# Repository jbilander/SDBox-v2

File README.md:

# SDBox v2
***
SDBox v2 for Amiga, hardware compatible with the new updated card-detect (insert/eject interrupt) firmware written by N.Ekström available here: https://github.com/niklasekstrom/amiga-par-to-spi-adapter

This version is superseded by the new SDBox-v3 here: https://github.com/jbilander/SDBox-v3
***

<br />

<br />

***

Here is a short video clip showing the new card detect feature: <br />
https://drive.google.com/file/d/11R0idJcfvWwsGSfzbPFG1xpoupvCA6SC/view?usp=sharing

***

### Howto build the SDBox Rev2...

***

Start by soldering the `U2` and `U3` ICs, then the passives, the card holder, micro-usb jack, DB25M and so on, nothing complicated, but do skip the 6-pin ICSP-header on the Nano if you're going to put this in a 3D-printed case...

***

***

At this stage, before you solder the Nano down to the board, you should verify that `+5V` via the Micro-USB jack is ok...

***

***

Now the Nano, validate `+5V` and `+3.3V` is ok on the Nano:

Powering the MicroSD card directly from the 3.3V-pin of the Arduino, are you nuts?

Well, maybe, but typical SD card current consumption is `~30mA` in SPI mode.
The Arduino Nano taps `3.3V` from the internal LDO `3V3OUT` supply of the `FT232RL` USB-chip, or in case of the clones the `CH340` USB-chip. 

    FT232RL: Up to 50mA can be drawn from this pin to power external logic if required.
    CH340G: Maximum output current is 30mA, and that voltage stays rather stable up to about 30mA.
***

***

Time to build and flash the firmware:

***

<br />

***

And we need to 3D-print a case for it before we put the LEDs in, don't we?...

(STL-files available in the DSM folder)

***

***

Final result:
<br />

***

Comparison with `v1`, look at the difference in size:
<br />

***

Now time to build the new `spisd.device` driver, add `+kick13` to the `build.bat` if default is set to build for AmigaOS 2.0...

(`VBCC` for Windows I downloaded from here (Thanks: Leffmann for the installer), https://eab.abime.net/showthread.php?t=83113 )

***

***

BOM Rev. 2A
---------
Position  | Name/Value   | Package | Notes
-|-|-|-|
U1 | Arduino Nano V3 | |
U2 | 74LVC3G17 | TSSOP-8_3x3mm_P0.65mm | Triple non-inverting Schmitt trigger with 5V tolerant input [74LVC3G17](https://www.mouser.com/ProductDetail/771-LVC3G17DP125)
U3 | 74AHCT1G17 | 5-TSSOP, SC-70-5, SOT-353  (2.0 mm × 1.25mm) | Single non-inverting Schmitt trigger [74AHCT1G17GWH](https://www.mouser.com/ProductDetail/771-74AHCT1G17GWH)
J1 | D-Sub DB25M | DB25 Male connector with solder lugs | DB25 for Amiga parallel port
J2 | Micro USB connector | USB Micro B SMT | For +5V Power, (style 1) <br />https://www.aliexpress.com/item/32991869539.html
J3 | Micro SD Card Holder | 9-pin Micro SD card slot connector | https://www.aliexpress.com/item/32802051702.html
D1 (Optional) | LED 3mm | PinHeader_1x02_P2.54mm_Vertical, pin pitch 2.54 mm | SD Activity LED indicator, Diffused Orange / Amber, 1.8V-2.3V, 20-30 mA, 605-610nm
D2 (Optional) | LED 3mm | PinHeader_1x02_P2.54mm_Vertical, pin pitch 2.54 mm | Power LED indicator, Green Diffused T-1, 25 mcd, 565 nm, 2.2 V, 25 mA
R1 (Optional) | 150 Ohm Resistor | 1206 SMD, 200 mW | (Mandatory if D1 populated) Series resistor for D1 LED, adjust R-value to your type of LED and preferred brightness
R2 (Optional) | 150 Ohm Resistor | 1206 SMD, 200 mW | (Mandatory if D2 populated) Series resistor for D2 LED, adjust R-value to your type of LED and preferred brightness
R3 | 10k Ohm Resistor | 1206 SMD | Pull-up (to VCC) resistor for /SS
R4 (Optional) | 10k Ohm Resistor | 1206 SMD | Pull-up (to VCC) resistor for MOSI
R5 | 10k Ohm Resistor | 1206 SMD | Pull-up (to 3V3) for MISO_3V3
R6 | 10k Ohm Resistor | 1206 SMD | Pull-up (to 3V3) for DAT1 pin 8 on MicroSD-holder
R7 | 10k Ohm Resistor | 1206 SMD | Pull-up (to 3V3) for DAT2 pin 1 on MicroSD-holder
JP1 (Optional) | 0 Ohm Resistor, or Solder Blob | 1206 SMD | Populate this one to reset Nano in conjunction with Ctrl-Amiga-Amiga
C1 | 220uF Capacitor | SMD-Tantalum, 4.3 x 7.3 x 2.8 mm | Capacitor for VIN +5V Power via USB https://www.reichelt.com/se/en/smd-tantalum-220-f-10v-125-c-t491d-220u-10-p206492.html
C2 | 0.1uF = 100nF Capacitor | 0805 SMD | Decoupling capacitor for U2
C3 | 0.1uF = 100nF Capacitor | 0805 SMD | Decoupling capacitor for U3
C4 | 0.1uF = 100nF Capacitor | 0805 SMD | Decoupling capacitor for J3

***

### Howto get 5V from the Amigas external floppy port _(250 mA max)_, let's make a cable...

<br />

***
I did't have a `DB23` Male connector so I used a `DB25` and cut it down to a 23 with a hacksaw. I cut on the left side (pin 1 and 14) so that the plug will clear the neighbouring RCA-jack when plugged into the A500 external floppy drive port.
***

***
Remove pin 1 and 14, wiggle back and forth with a plier until they exhaust and snap then pull out the remains from the other side
***

***
Cut and wirestrip the micro-usb cable. Verify polarity, normally black is GND and red is +5V but the cable mfg might have mixed up the wire colours so check with a multimeter to be certain. Pin 3-7 on the connector is GND on the Amiga, +5V is on pin 12. You could either Blob pin 3-7 together (requires quite a lot of solder) and then solder the micro-usb GND-wire to that Blob or do as I did below with 5 individual wires soldered and crimped together.
***

***
Some shrink tube on, a bit overkill maybe but hey it's a guide, no shortcuts, I even crimped AND soldered the GND-joint :)
***

***
Ready to go and it clears both the RCA-plug and the serial port connector. With this cable now plugged into the SDBox it'll be powered on as soon as the Amiga is powered on and vice versa.
***

***

Happy Hackin'

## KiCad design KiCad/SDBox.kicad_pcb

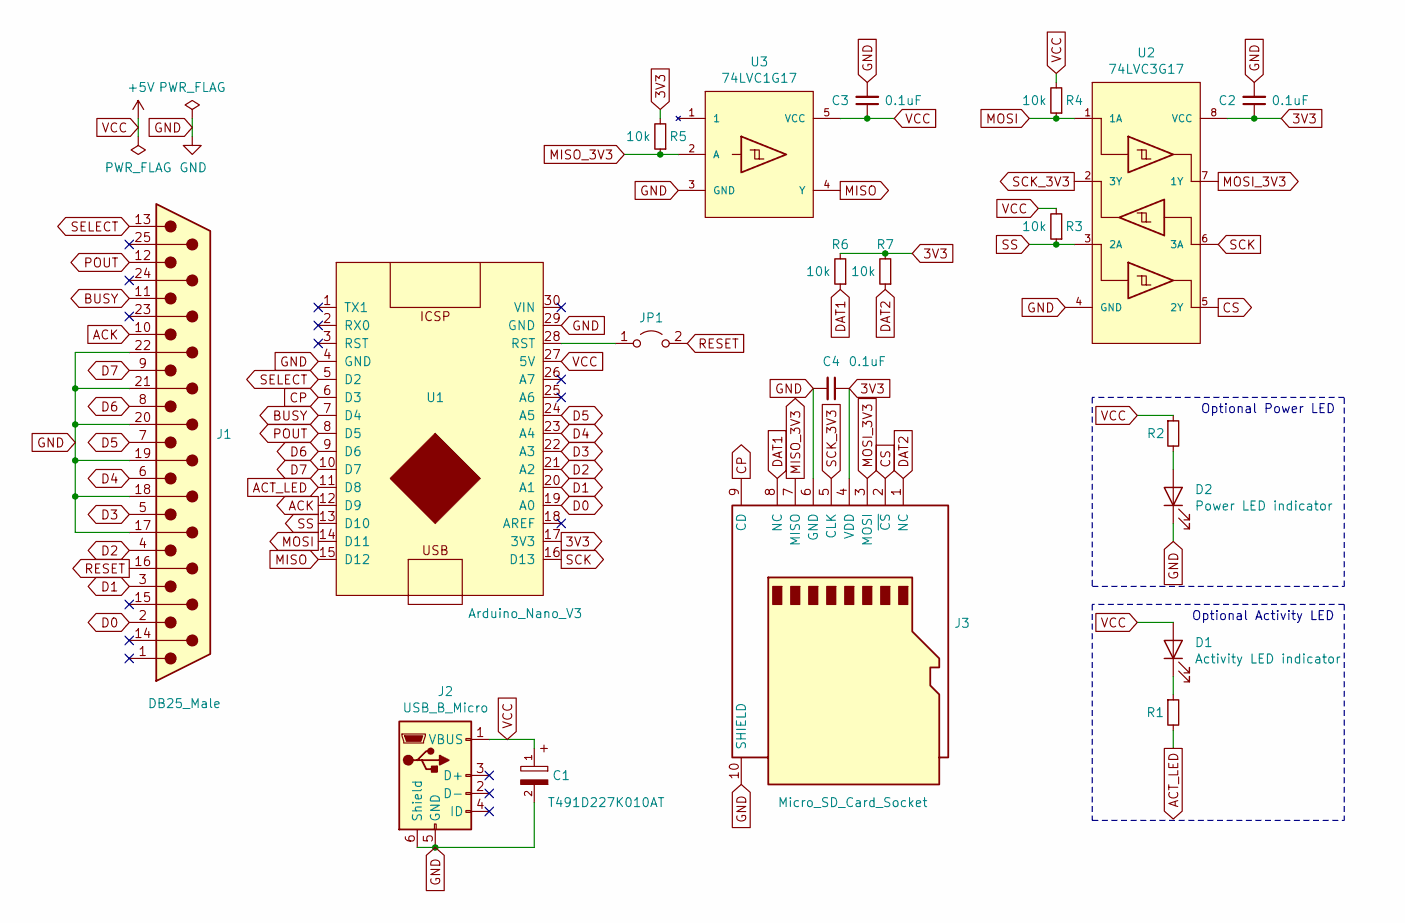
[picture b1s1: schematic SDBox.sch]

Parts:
C1: T491D227K010AT; CAPMP7343X430N
C2, C3, C4: 0.1uF; C_0805_2012Metric_Pad1.15x1.40mm_HandSolder
D1: Activity LED indicator; LED_D3.0mm
D2: Power LED indicator; LED_D3.0mm
J1: DB25_Male; DSUB-25_Male_EdgeMount_P2.77mm
J2: USB_B_Micro; USB_Micro-B_Unknown_5s_SMT
J3: Micro_SD_Card_Socket; GCT-MEM2055-00-190-01-A
JP1: Jumper_2_Open; R_1206_3216Metric_Pad1.42x1.75mm_HandSolder
R1, R2: 150; R_1206_3216Metric_Pad1.42x1.75mm_HandSolder
R3, R4, R5, R6, R7: 10k; R_1206_3216Metric_Pad1.42x1.75mm_HandSolder
U1: Arduino_Nano_V3
U2: 74LVC3G17; TSSOP-8_3x3mm_P0.65mm_Custom_Handsoldering
U3: 74LVC1G17; SOT-353_SC-70-5_Custom_Handsoldering

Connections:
3V3: C2.1, C4.1, J3.4 (VDD), R5.2, R6.2, R7.2, U1.17 (3V3), U2.8 (VCC)
ACK: J1.10, U1.12 (D9)
ACT_LED: R1.2, U1.11 (D8)
BUSY: J1.11, U1.7 (D4)
CP: J3.9 (CD), U1.6 (D3)
CS: J3.2 (~CS), U2.5 (2Y)
D0: J1.2, U1.19 (A0)
D1: J1.3, U1.20 (A1)
D2: J1.4, U1.21 (A2)
D3: J1.5, U1.22 (A3)
D4: J1.6, U1.23 (A4)
D5: J1.7, U1.24 (A5)
D6: J1.8, U1.9 (D6)
D7: J1.9, U1.10 (D7)
DAT1: J3.8 (NC), R6.1
DAT2: J3.1 (NC), R7.1
GND: C1.2, C2.2, C3.2, C4.2, D2.1 (K), J1.17, J1.18, J1.19, J1.20, J1.21, J1.22, J2.5 (GND), J2.6 (Shield), J3.6 (GND), J3.10 (SHIELD), U1.4 (GND), U1.29 (GND), U2.4 (GND), U3.3 (GND)
MISO: U1.15 (D12), U3.4 (Y)
MISO_3V3: J3.7 (MISO), R5.1, U3.2 (A)
MOSI: R4.1, U1.14 (D11), U2.1 (1A)
MOSI_3V3: J3.3 (MOSI), U2.7 (1Y)
unnamed: D1.1 (K), R1.1
unnamed: D2.2 (A), R2.2
unnamed: JP1.1 (A), U1.28 (RST)
POUT: J1.12, U1.8 (D5)
RESET: J1.16, JP1.2 (B)
SCK: U1.16 (D13), U2.6 (3A)
SCK_3V3: J3.5 (CLK), U2.2 (3Y)
SELECT: J1.13, U1.5 (D2)
SS: R3.1, U1.13 (D10), U2.3 (2A)
VCC: C1.1, C3.1, D1.2 (A), J2.1 (VBUS), R2.1, R3.2, R4.2, U1.27 (5V), U3.5 (VCC)

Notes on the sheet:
Optional Activity LED
Optional Power LED

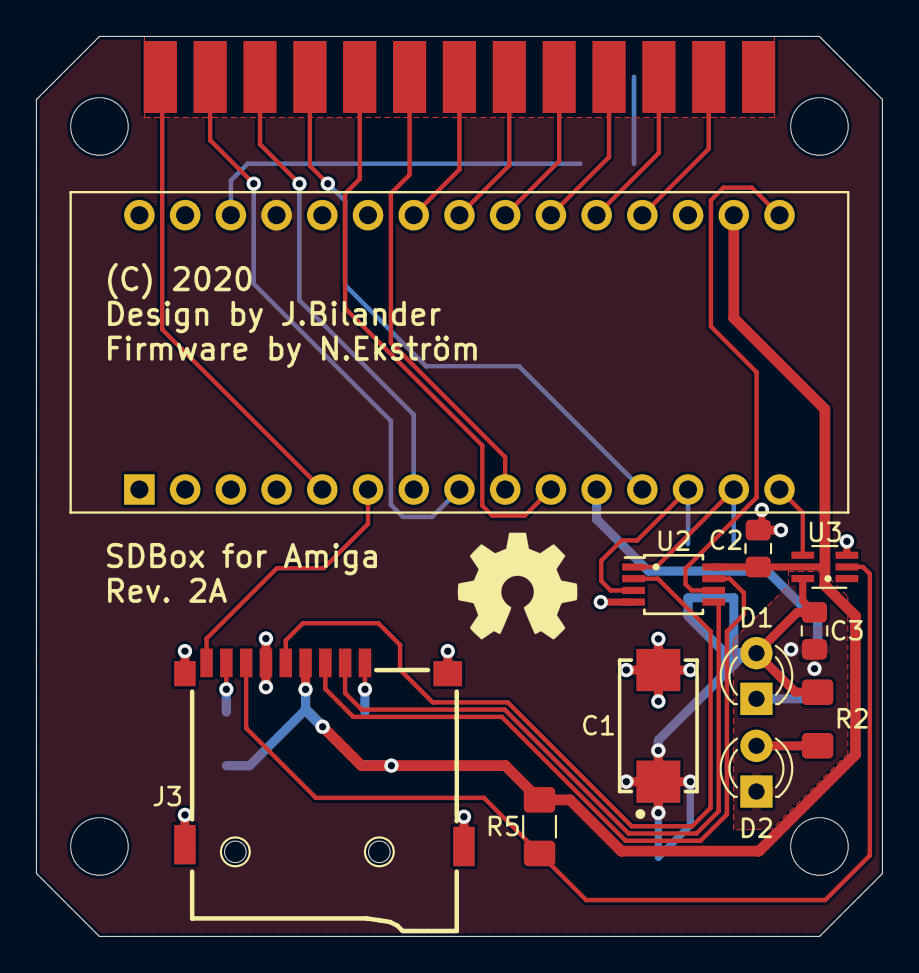
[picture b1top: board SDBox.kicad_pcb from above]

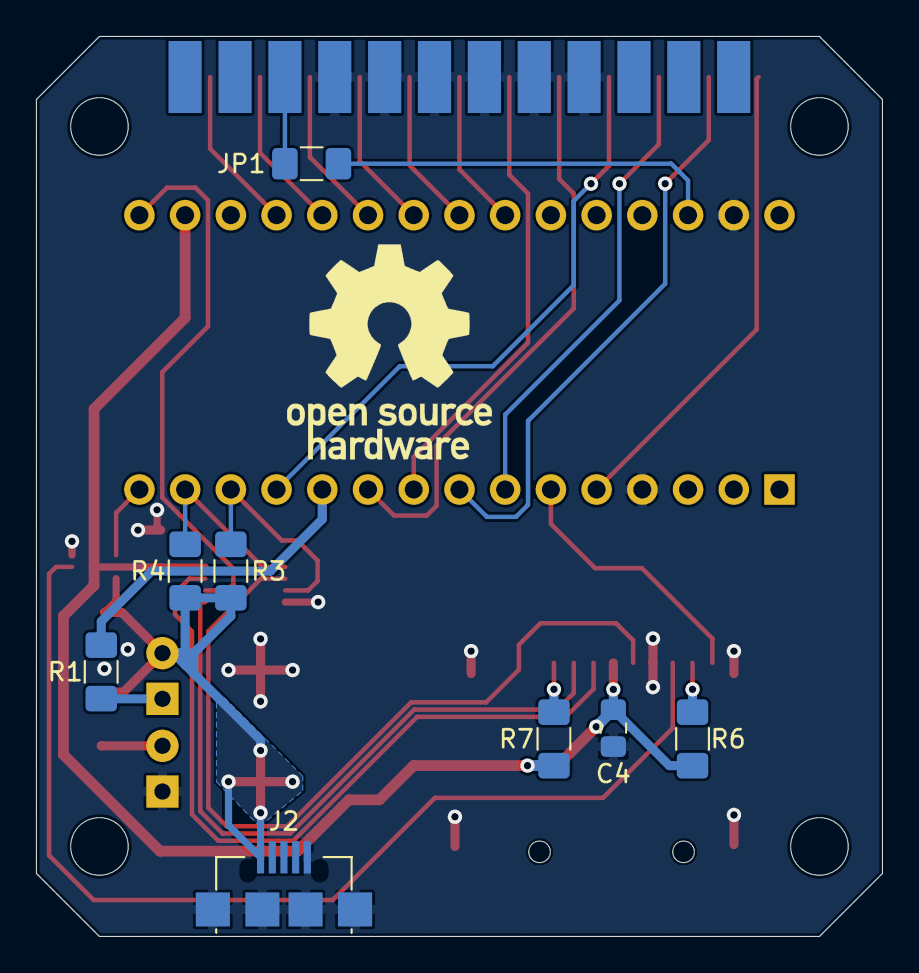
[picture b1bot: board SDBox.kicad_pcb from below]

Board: 2 copper layers, 47.0 x 50.0 mm, 20 parts (8 on the bottom side), 31 nets.

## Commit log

2021-08-04 added footprints
2021-08-04 added KiCad files
2021-08-04 added schematic pdf
2021-08-06 added pics
2021-08-06 small improvement 3V3-routing
2021-09-30 Added source file SDBox-v2 case made in DesignSpark Mechanical 5.0
2021-09-30 Added source file SDBox-text imported into DSM 5.0 from SketchUp and fixed by me
2021-09-30 Added source file SDBox-text made in SketchUp Make 2017
2021-09-30 Added generated stl files for 3D-printing SDBox-v2 case
2021-10-11 added .step files
2021-10-11 Added new exported STEP-files

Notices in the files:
KiCad/SDBox.kicad_pcb:
(C) 2020
